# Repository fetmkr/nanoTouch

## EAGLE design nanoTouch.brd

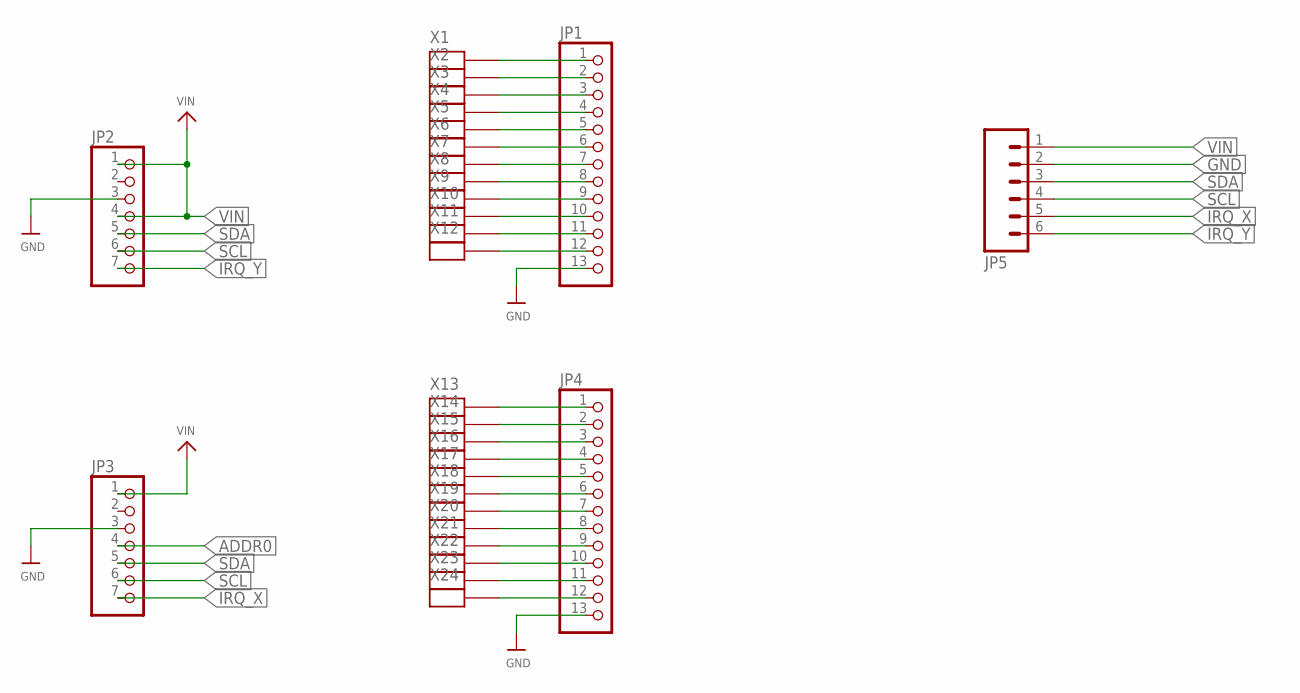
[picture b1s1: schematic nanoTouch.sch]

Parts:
JP1, JP4: HEADER-1X13; 1X13_ROUND_70
JP2, JP3: HEADER-1X770MIL; 1X07_ROUND_70
JP5: M06SILK_FEMALE_PTH; 1X06
X1, X2, X3, X4, X5, X6, X7, X8, X9, X10, X11, X12, X13, X14, X15, X16, X17, X18, X19, X20, X21, X22, X23, X24: PAD-2X2; PAD2X2

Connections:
ADDR0: JP3.4
GND: JP1.13, JP2.3, JP3.3, JP4.13, JP5.2
IRQ_X: JP3.7, JP5.5
IRQ_Y: JP2.7, JP5.6
unnamed: JP1.1, X1.P$1
unnamed: JP1.2, X2.P$1
unnamed: JP1.3, X3.P$1
unnamed: JP1.4, X4.P$1
unnamed: JP1.5, X5.P$1
unnamed: JP1.6, X6.P$1
unnamed: JP1.7, X7.P$1
unnamed: JP1.8, X8.P$1
unnamed: JP1.9, X9.P$1
unnamed: JP1.10, X10.P$1
unnamed: JP1.11, X11.P$1
unnamed: JP1.12, X12.P$1
unnamed: JP4.1, X13.P$1
unnamed: JP4.2, X14.P$1
unnamed: JP4.3, X15.P$1
unnamed: JP4.4, X16.P$1
unnamed: JP4.5, X17.P$1
unnamed: JP4.6, X18.P$1
unnamed: JP4.7, X19.P$1
unnamed: JP4.8, X20.P$1
unnamed: JP4.9, X21.P$1
unnamed: JP4.10, X22.P$1
unnamed: JP4.11, X23.P$1
unnamed: JP4.12, X24.P$1
SCL: JP2.6, JP3.6, JP5.4
SDA: JP2.5, JP3.5, JP5.3
VIN: JP2.1, JP2.4, JP3.1, JP5.1

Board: 2 copper layers, 29 parts (0 on the bottom side), 30 nets, no tracks yet.

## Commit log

2016-04-10 :tada: Added .gitattributes
2016-04-10 first

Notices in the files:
parts and their libraries:
microbuilder: This work is placed in the public domain, and may be freely used for commercial and non-commercial work with the following conditions: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
